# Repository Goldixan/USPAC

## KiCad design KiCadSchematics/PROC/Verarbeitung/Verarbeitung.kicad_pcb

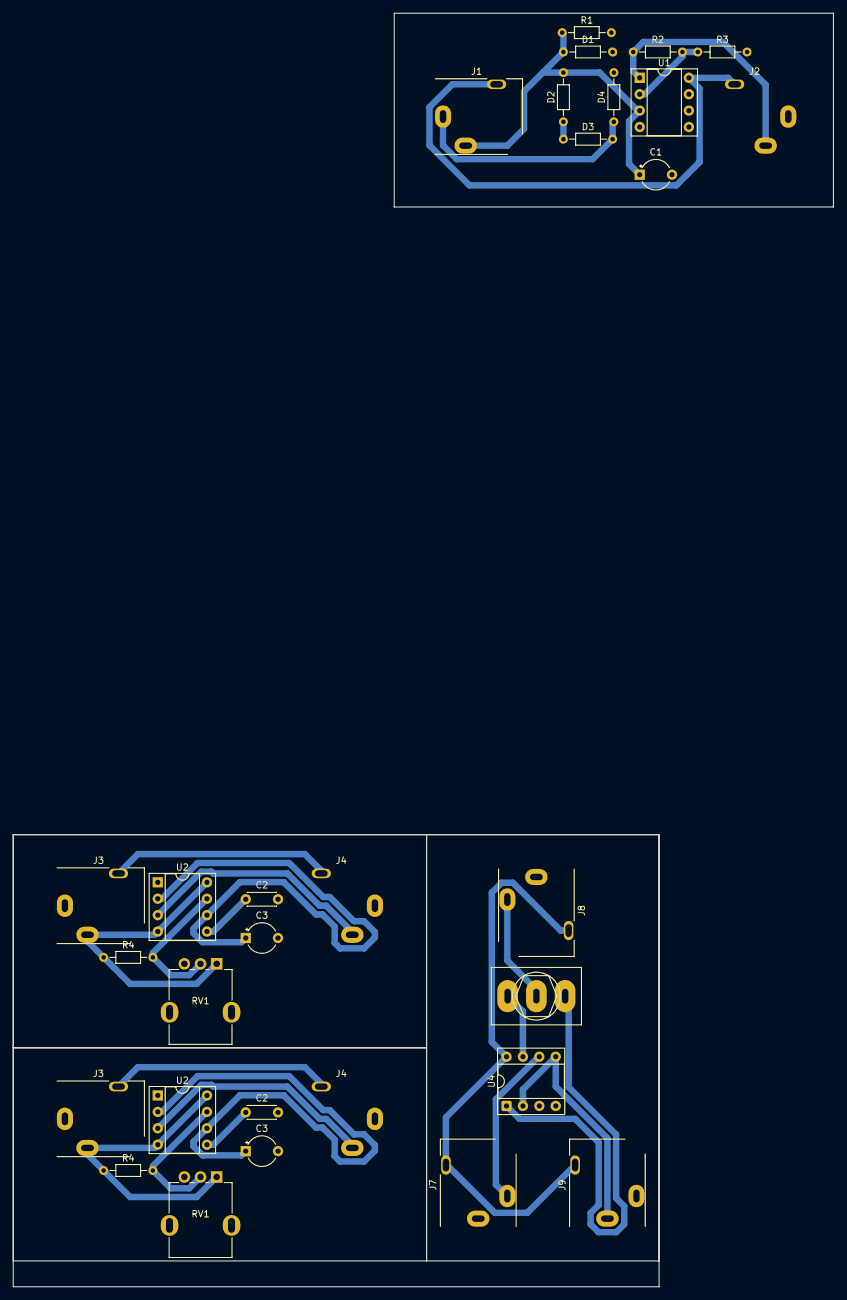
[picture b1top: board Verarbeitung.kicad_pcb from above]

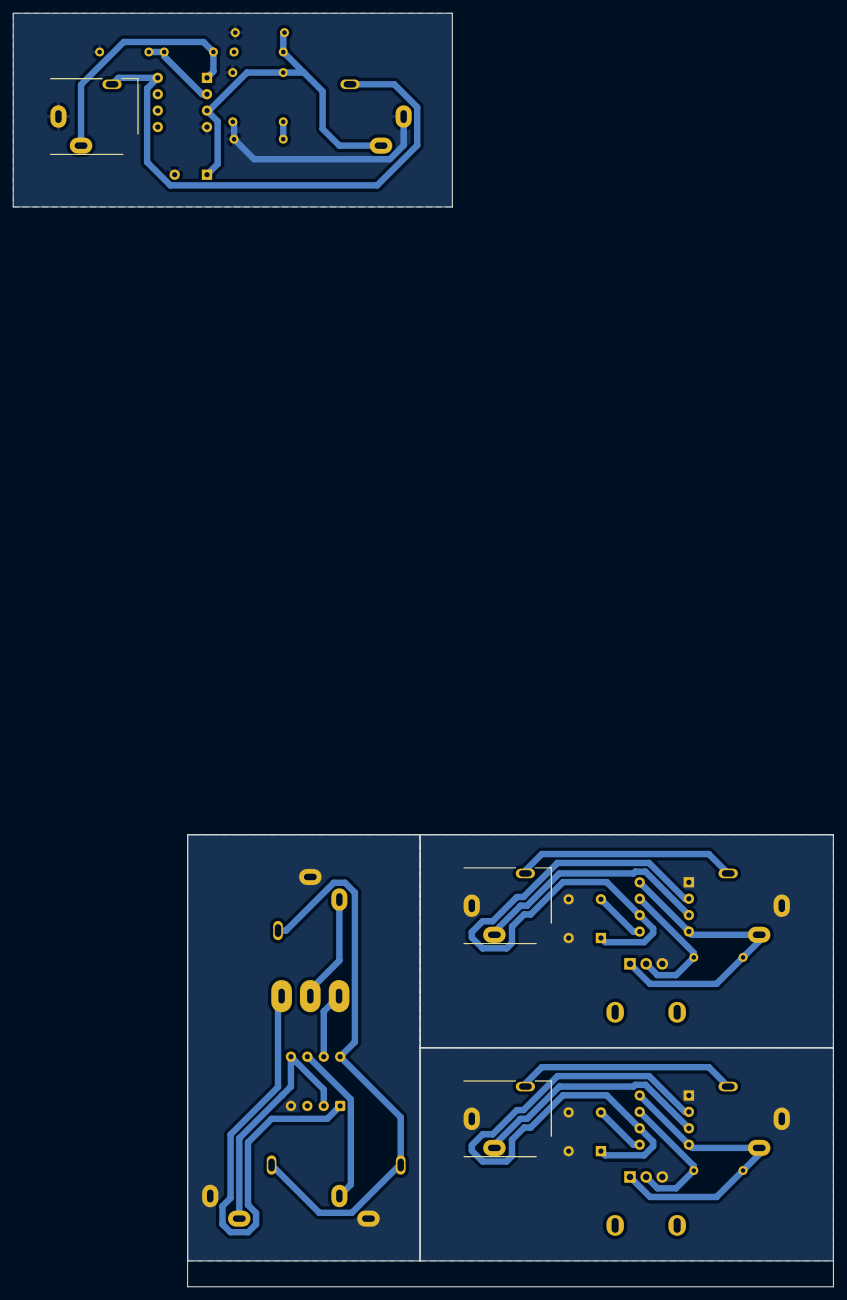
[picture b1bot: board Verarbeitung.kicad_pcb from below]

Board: 2 copper layers, 127.0 x 197.2 mm, 30 parts (3 on the bottom side), 17 nets.

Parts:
C1: 1000uF; CP_Radial_Tantal_D4.5mm_P5.00mm
C2, C2#2: 10nF; C_Disc_D4.3mm_W1.9mm_P5.00mm
C3, C3#2: 47uF; CP_Radial_Tantal_D4.5mm_P5.00mm
D1, D2, D3, D4: D; R_Axial_DIN0204_L3.6mm_D1.6mm_P7.62mm_Horizontal
J1, J2, J3, J3#2, J4, J4#2, J7, J8, J9: AudioJack3; Jack_3.5mm_CUI_SJ1-3513N_Horizontal
R1: 10k; R_Axial_DIN0204_L3.6mm_D1.6mm_P7.62mm_Horizontal
R2: 1k; R_Axial_DIN0204_L3.6mm_D1.6mm_P7.62mm_Horizontal
R3: 2.8k; R_Axial_DIN0204_L3.6mm_D1.6mm_P7.62mm_Horizontal
R4, R4#2: R; R_Axial_DIN0204_L3.6mm_D1.6mm_P7.62mm_Horizontal
RV1, RV1#2: 100k; Potentiometer_RV09
SW2: SW_SPDT; SW_Toggle_Blue_wSlots
U1, U4: MCP6002; DIP-8_W7.62mm_Socket
U2, U2#2: NE555P; DIP-8_W7.62mm_Socket

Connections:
5V: J1.R, J2.R, J7.R, J8.R, J9.R, U1.8 (V+), U4.8 (V+)
GND: C1.2, C2.2, C2#2.2, C3.2, C3#2.2, D3.2 (A), D4.2 (A), J1.S, J2.S, J3.S, J3#2.S, J4.S, J4#2.S, J7.S, J8.S, J9.T, R1.2, R3.2, RV1.3, RV1#2.3, U1.4 (V-), U2.1 (GND), U2#2.1 (GND), U4.4 (V-)
unnamed: C1.1, D1.1 (K), D2.1 (K), R1.1, U1.3 (+)
unnamed: J2.T, R2.1, U1.1
unnamed: J3.R, J3#2.R, J4.R, J4#2.R
unnamed: SW2.1 (A), U4.1
unnamed: J8.T, SW2.2 (B)
unnamed: SW2.3 (C), U4.7
unnamed: R2.2, R3.1, U1.2 (-)
unnamed: C2.1, C2#2.1, U2.5 (CV), U2#2.5 (CV)
unnamed: R4.2, R4#2.2, RV1.2, RV1#2.2, U2.7 (DIS), U2#2.7 (DIS)
unnamed: J4.T, J4#2.T, U2.3 (Q), U2#2.3 (Q)
unnamed: J3.T, J3#2.T, R4.1, R4#2.1, RV1.1, RV1#2.1, U2.4 (R), U2.8 (VCC), U2#2.4 (R), U2#2.8 (VCC)
unnamed: C3.1, C3#2.1, U2.2 (TR), U2.6 (THR), U2#2.2 (TR), U2#2.6 (THR)
unnamed: J7.T, U4.3 (+), U4.6 (-)
unnamed: J9.S, U4.2 (-), U4.5 (+)
Signal: D1.2 (A), D2.2 (A), D3.1 (K), D4.1 (K), J1.T

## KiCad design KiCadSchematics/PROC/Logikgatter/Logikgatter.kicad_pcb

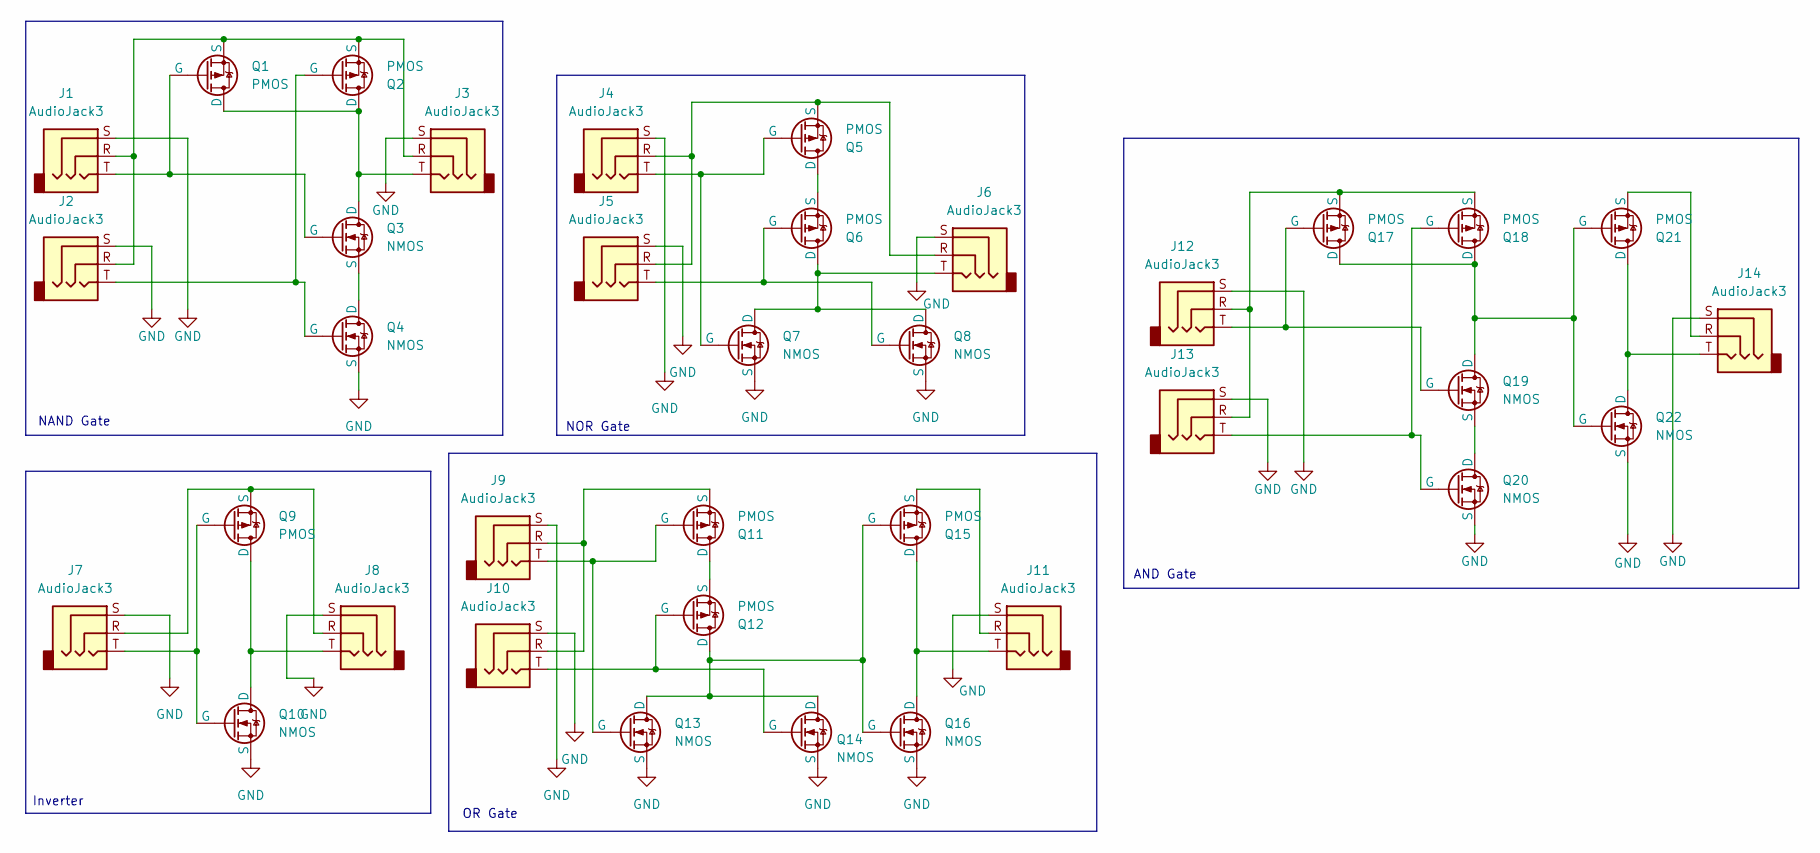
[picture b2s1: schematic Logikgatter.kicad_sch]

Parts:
J1, J2, J3, J4, J5, J6, J7, J8, J9, J10, J11, J12, J13, J14: AudioJack3; Jack_3.5mm_CUI_SJ1-3513N_Horizontal
Q1, Q2, Q5, Q6, Q9, Q11, Q12, Q15, Q17, Q18, Q21: PMOS; SOT54ES
Q3, Q4, Q7, Q8, Q10, Q13, Q14, Q16, Q19, Q20, Q22: NMOS; SOT54ES

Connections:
GND: J1.S, J2.S, J3.S, J4.S, J5.S, J6.S, J7.S, J8.S, J9.S, J10.S, J11.S, J12.S, J13.S, J14.S, Q4.3 (S), Q7.3 (S), Q8.3 (S), Q10.3 (S), Q13.3 (S), Q14.3 (S), Q16.3 (S), Q20.3 (S), Q22.3 (S)
unnamed: J3.T, Q1.1 (D), Q2.1 (D), Q3.1 (D)
unnamed: J1.T, Q1.2 (G), Q3.2 (G)
unnamed: J1.R, J2.R, J3.R, Q1.3 (S), Q2.3 (S)
unnamed: J2.T, Q2.2 (G), Q4.2 (G)
unnamed: Q3.3 (S), Q4.1 (D)
unnamed: Q5.1 (D), Q6.3 (S)
unnamed: J4.T, Q5.2 (G), Q7.2 (G)
unnamed: J4.R, J5.R, J6.R, Q5.3 (S)
unnamed: J6.T, Q6.1 (D), Q7.1 (D), Q8.1 (D)
unnamed: J5.T, Q6.2 (G), Q8.2 (G)
unnamed: J7.R, J8.R, Q9.3 (S)
unnamed: J8.T, Q9.1 (D), Q10.1 (D)
unnamed: J7.T, Q9.2 (G), Q10.2 (G)
unnamed: Q11.1 (D), Q12.3 (S)
unnamed: J9.T, Q11.2 (G), Q13.2 (G)
unnamed: J9.R, J10.R, Q11.3 (S)
unnamed: Q12.1 (D), Q13.1 (D), Q14.1 (D), Q15.2 (G), Q16.2 (G)
unnamed: J10.T, Q12.2 (G), Q14.2 (G)
unnamed: J11.T, Q15.1 (D), Q16.1 (D)
unnamed: J11.R, Q15.3 (S)
unnamed: Q17.1 (D), Q18.1 (D), Q19.1 (D), Q21.2 (G), Q22.2 (G)
unnamed: J12.T, Q17.2 (G), Q19.2 (G)
unnamed: J12.R, J13.R, Q17.3 (S), Q18.3 (S)
unnamed: J13.T, Q18.2 (G), Q20.2 (G)
unnamed: Q19.3 (S), Q20.1 (D)
unnamed: J14.T, Q21.1 (D), Q22.1 (D)
unnamed: J14.R, Q21.3 (S)

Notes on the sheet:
NOR Gate
OR Gate
Inverter
NAND Gate
AND Gate

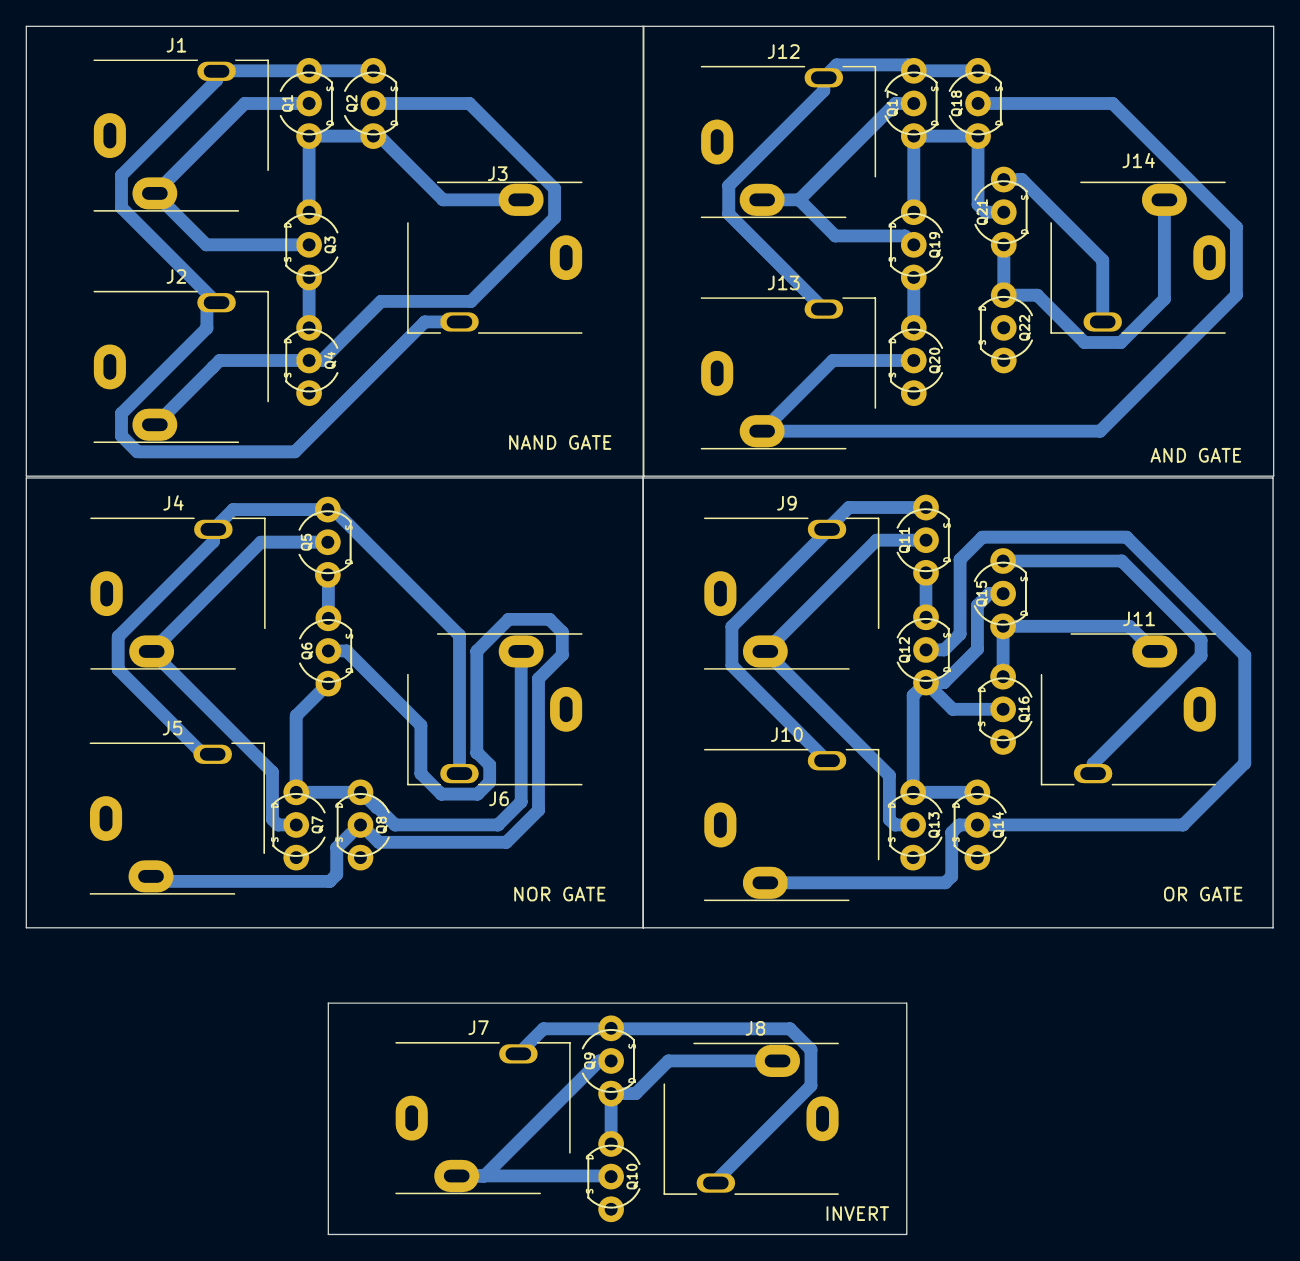
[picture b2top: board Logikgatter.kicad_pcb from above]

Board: 2 copper layers, 97.1 x 94.0 mm, 36 parts (0 on the bottom side), 28 nets.

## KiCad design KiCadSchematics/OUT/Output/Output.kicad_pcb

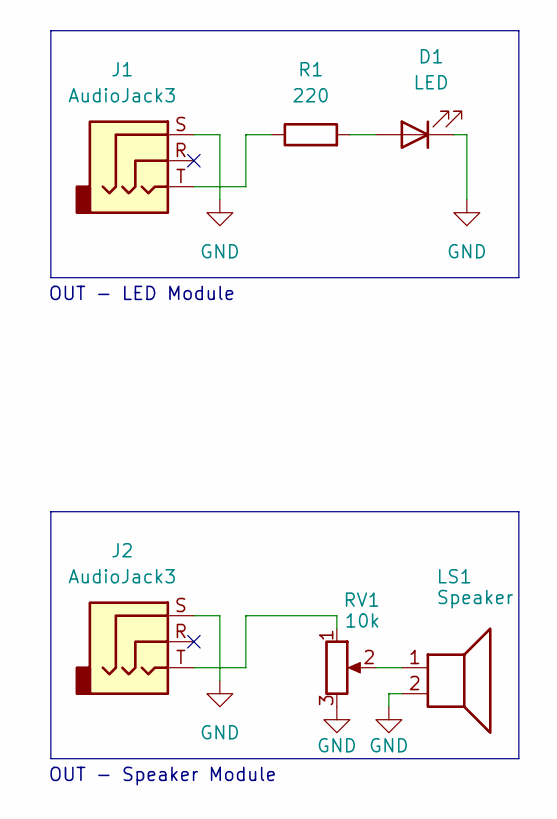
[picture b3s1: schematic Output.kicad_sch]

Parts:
D1: LED; LED_D3.0mm
J1, J2: AudioJack3; Jack_3.5mm_CUI_SJ1-3513N_Horizontal
LS1: Speaker; R_Axial_DIN0204_L3.6mm_D1.6mm_P7.62mm_Horizontal
R1: 220; R_Axial_DIN0204_L3.6mm_D1.6mm_P7.62mm_Horizontal
RV1: 10k; Potentiometer_RV09

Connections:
GND: D1.1 (K), J1.S, J2.S, LS1.2, RV1.3
unnamed: D1.2 (A), R1.2
unnamed: J1.T, R1.1
unnamed: J2.T, RV1.1
unnamed: LS1.1, RV1.2

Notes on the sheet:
OUT - LED Module
OUT - Speaker Module

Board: 2 copper layers, 6 parts (0 on the bottom side), 5 nets, no tracks yet.
